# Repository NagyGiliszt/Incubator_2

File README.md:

# Incubator V.:2.1.0 
Atmega328 mikrokontrollerrel felépített inkubátor.
Használd, alakítsd át belátásod szerint, de egy kikötésem van: 
Felelősséget nem vállalok, sem jelen verzióért, sem az esetleges további átalakításokért és/vagy verziókért.
Minden esetleges kár TÉGED terhel!
Természetesen nem fogok pénzt kérni, hogy használhasd a terveket/forráskódot.
Viszont, ha forrásaid és kedved megengedik, támogathatsz.
Kérdésekkel, esetleges támogatáshoz szükséges információkkal keress a "nagytoldjano at gmail dot com" email címen

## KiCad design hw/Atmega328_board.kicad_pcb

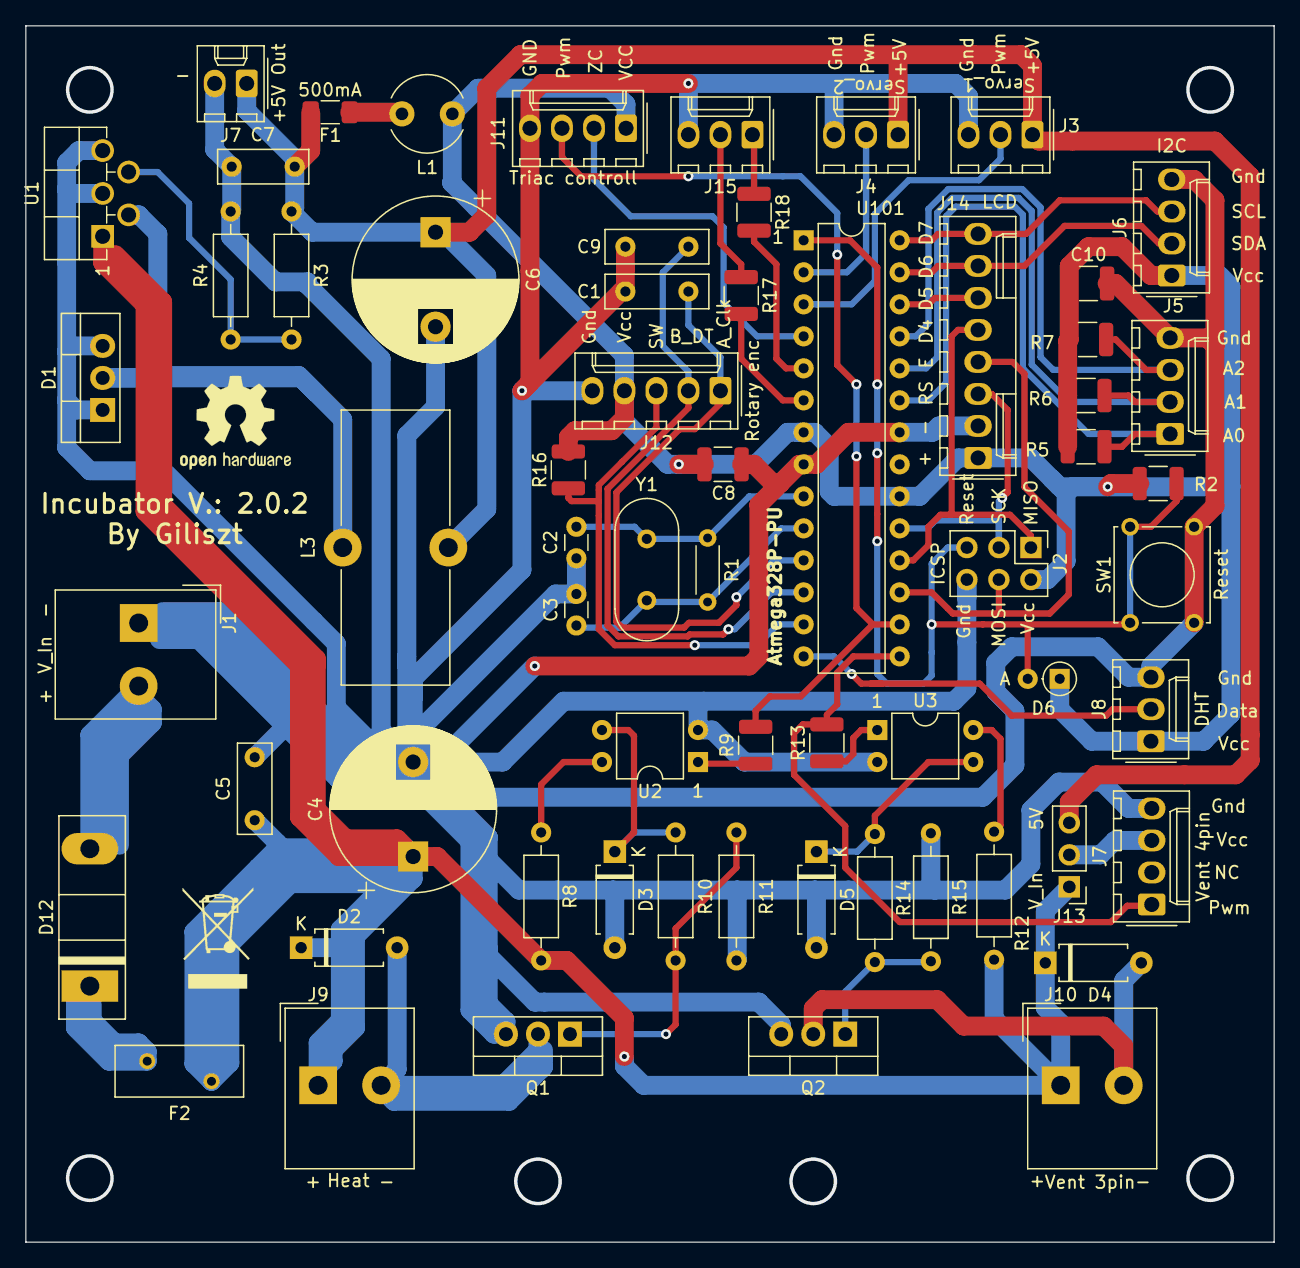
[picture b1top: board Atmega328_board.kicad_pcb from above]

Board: 2 copper layers, 99.1 x 96.5 mm, 63 parts (0 on the bottom side), 45 nets.

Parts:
C1, C9: 100n; C_Disc_D8.0mm_W2.5mm_P5.00mm
C2, C3: 22p; C_Disc_D3.0mm_W1.6mm_P2.50mm
C4, C6: 470u; CP_Radial_D13.0mm_P7.50mm
C5, C7: 100n; C_Disc_D7.0mm_W2.5mm_P5.00mm
C8, C10: 100n; C_1210_3225Metric
D1: Schottky; TO-220-3_Vertical
D2, D3, D4, D5: D_Schottky; D_A-405_P7.62mm_Horizontal
D6: 1N4148; D_DO-35_SOD27_P2.54mm_Vertical_AnodeUp
D12: 60V/20A; D_DO-247_Vertical
F1: 500mA; R_1206_3216Metric_Pad1.30x1.75mm_HandSolder
F2: 6,3A; Fuse_BelFuse_0ZRE0016FF_L9.9mm_W3.8mm
J1: V_In; Altech_AK300_1x02_P5.00mm_45-Degree
J2: ICSP; PinHeader_2x03_P2.54mm_Vertical
J3: Servo1; Molex_KK-254_AE-6410-03A_1x03_P2.54mm_Vertical
J4: Servo2; Molex_KK-254_AE-6410-03A_1x03_P2.54mm_Vertical
J5: NTC; Molex_KK-254_AE-6410-04A_1x04_P2.54mm_Vertical
J6: I2C; Molex_KK-254_AE-6410-04A_1x04_P2.54mm_Vertical
J7: 5V Out; Molex_KK-254_AE-6410-02A_1x02_P2.54mm_Vertical
J7#2: Vent_4pin; Molex_KK-254_AE-6410-04A_1x04_P2.54mm_Vertical
J8: DHT; Molex_KK-254_AE-6410-03A_1x03_P2.54mm_Vertical
J9: pwm_heat; Altech_AK300_1x02_P5.00mm_45-Degree
J10: pwm_vent; Altech_AK300_1x02_P5.00mm_45-Degree
J11: Triac; Molex_KK-254_AE-6410-04A_1x04_P2.54mm_Vertical
J12: Rotary enc; Molex_KK-254_AE-6410-05A_1x05_P2.54mm_Vertical
J13: Vent_Vcc; PinHeader_1x03_P2.54mm_Vertical
J14: LCD; Molex_KK-254_AE-6410-08A_1x08_P2.54mm_Vertical
J15: FrontLed; Molex_KK-254_AE-6410-03A_1x03_P2.54mm_Vertical
L1: 10uH; L_Radial_D6.0mm_P4.00mm
L3: 330u; L_Toroid_Vertical_L21.6mm_W8.4mm_P8.38mm_Pulse_G
Q1, Q2: IRLZ34N; TO-220-3_Vertical
R1: 1M; R_Axial_DIN0204_L3.6mm_D1.6mm_P5.08mm_Horizontal
R2, R5, R6, R7, R16: 10k; R_1210_3225Metric
R3: 3065; R_Axial_DIN0207_L6.3mm_D2.5mm_P10.16mm_Horizontal
R4: 1k; R_Axial_DIN0207_L6.3mm_D2.5mm_P10.16mm_Horizontal
R8, R11, R12, R15: 4k7; R_Axial_DIN0207_L6.3mm_D2.5mm_P10.16mm_Horizontal
R9, R13, R17, R18: 1k; R_1210_3225Metric
R10, R14: 100; R_Axial_DIN0207_L6.3mm_D2.5mm_P10.16mm_Horizontal
SW1: Reset; SW_Tactile_Straight_KSL0Axx1LFTR
U1: LM2596S-ADJ; TO-220F-5_P3.4x2.06mm_StaggerEven_Lead1.86mm_Vertical
U2, U3: EL817; DIP-4_W7.62mm
U101: ATmega328-PU; DIP-28_W7.62mm
Y1: 16MHz; Crystal_HC49-U_Vertical

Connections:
/5V: C6.1, C7.1, F1.2, J3.1, J4.1, J7.1, J13.3, L3.2, R3.1
/AD0: J5.1, R5.1, U101.23
/AD1: J5.2, R6.1, U101.24
/AD2: J5.3, R7.1, U101.25
/AD3: J14.6, U101.26
/AD4: J6.2, J14.7, U101.27
/AD5: J6.3, J14.8, U101.28
/A_Clk: C1.1, J12.1, U101.11
/B_DT: C9.1, J12.2, U101.12
/D0: J4.2, U101.2
/D1: J3.2, U101.3
/D3: R18.2, U101.5
/D8: J8.2, U101.14
/D9: J7#2.1, R13.2, U101.15
/ERR_LED: R17.2, U101.6
/MISO: J2.1, J14.5, U101.18
/MOSI: J2.4, J14.4, U101.17
/Reset: D6.2, J2.5, R2.2, SW1.1, U101.1
/SCK: J2.3, J14.3, U101.19
/SW: J12.3, R16.1, U101.13
/Triac_PWM: J11.3, R9.2, U101.16
/VCC: C8.1, C10.1, D6.1, J2.2, J6.1, J8.1, J11.1, J12.4, J14.1, L1.1, R2.1, R5.2, R6.2, R7.2, R16.2, U101.7, U101.20
/V_In: C4.1, C5.1, D2.1, D4.1, F2.1, J9.1, J10.1, J13.1, R8.1, R12.1, U1.1
/ZC: J11.2, U101.4
GND: C1.2, C2.1, C3.1, C4.2, C5.2, C6.2, C7.2, C8.2, C9.2, C10.2, D1.1, D1.3, D3.2, D5.2, J1.1, J2.6, J3.3, J4.3, J5.4, J6.4, J7.2, J7#2.4, J8.3, J11.4, J12.5, J14.2, J15.3, Q1.3, Q2.3, R4.2, R11.2, R15.2, SW1.2, U1.3, U1.5, U2.2, U3.2, U101.8, U101.22
unnamed: C2.2, R1.1, U101.9, Y1.1
unnamed: C3.2, R1.2, U101.10, Y1.2
unnamed: D1.2, L3.1, U1.2
unnamed: D2.2, J9.2, Q1.2
unnamed: D3.1, R10.1, U2.3
unnamed: D4.2, J10.2, Q2.2
unnamed: D5.1, R14.1, U3.3
unnamed: D12.1, F2.2
unnamed: D12.2, J1.2
unnamed: F1.1, L1.2
unnamed: J7#2.3, J13.2
unnamed: J15.1, R18.1
unnamed: J15.2, R17.1
unnamed: Q1.1, R10.2, R11.1
unnamed: Q2.1, R14.2, R15.1
unnamed: R3.2, R4.1, U1.4
unnamed: R8.2, U2.4
unnamed: R9.1, U2.1
unnamed: R12.2, U3.4
unnamed: R13.1, U3.1

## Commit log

2021-07-25 Create src
